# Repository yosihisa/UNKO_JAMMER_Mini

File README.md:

# UNKO_JAMMER_Mini  
UNKO_JAMMER_Mini is a camera infrared　remote control. It can also handle washlets.  
It is compatible with Nikon, Canon, Sony and LIXIL.  
This repository is the source code of infrared remote control of the camera. (With washlette jack function)  
Video is [here](https://twitter.com/n_yosihisa/status/977338885901508608).  

# ウンコジャマー ミニとは
ウンコジャマーはカメラ用赤外線リモコンです。ウォシュレットを操作することもできます。  
Niko・Canon,Sonyの撮影コマンドとLIXILのおしりコマンドに対応しています。  
PENTAXは今後のアップデートで対応予定です。  
動画は[こちら](https://twitter.com/n_yosihisa/status/977338885901508608)です。

## 各部名称  

## 使い方
### 準備 
コイン型リチウム電池(CR2032)を電池ボックスにセットします。  
電池の上にある黒いスイッチの白のつまみを利用するカメラのメーカーに合わせます。  

メーカー対応表  

|メーカー  |スイッチ1(上)  |スイッチ2(下)  |
|---|---|---|
|Nikon  |OFF(左)  |OFF(左)  |
|Canon  |ON (右)  |OFF(左)  |
|Sony   |OFF (左) |ON (右)  |
|PENTAX |ON (右)  |ON (右)  |

### 撮影する
カメラをリモコン操作モードにします。(各機種の取扱説明書をご覧ください。)  
左側のスライドスイッチをONにします。  
LEDの下にある白いボタンを押すとシャッターを切ることができます。  
撮影が終了したら左側のスライドスイッチをoFFにしましょう。  

### おしりコマンドを発動する
おしりコマンドを発動するためには白いボタンを押しながら電源を入れる必要があります。  
白いボタンを押したまま電源を入れると、電源を切るまで白いボタンを押すたびにおしりコマンドが送信されます。

## 開発環境
- Atmel Studio 7
- KiCad 5.0.0
## 作者
よしひさ([@n_yosihisa](https://twitter.com/n_yosihisa))  
てぽ丼([@teppodone](https://twitter.com/teppodone))

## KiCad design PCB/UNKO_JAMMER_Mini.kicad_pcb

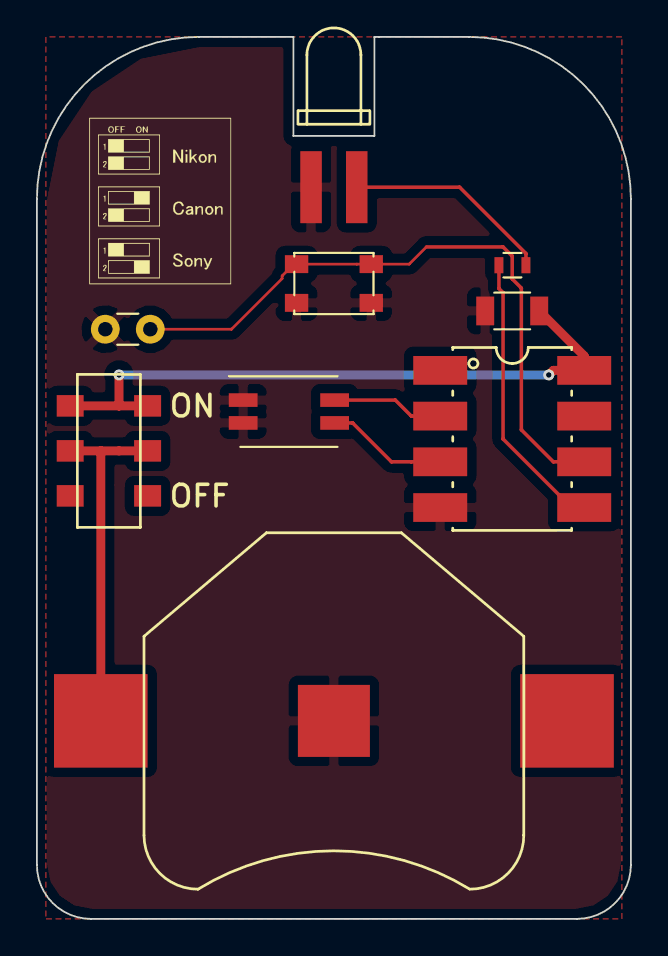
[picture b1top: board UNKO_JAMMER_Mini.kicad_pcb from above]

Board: 2 copper layers, 33.0 x 49.0 mm, 9 parts (0 on the bottom side), 8 nets.

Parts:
BT1: C2032; BC-2001
C1: 100u; C_1206
D1: LED; 3mmLED
IC1: ATTINY10-P; DIP_SMD-8
J1: Remote; C_Disc_D3.0mm_W1.6mm_P2.50mm
R1: 100; R_0603
SW1: POWER; SSSS213202_parallel
SW2: RELEASE; SKRPACE010_kai
SW3: ModeSelector; SW_DIP_x2_W5.08mm_Slide_Copal_CHS-A

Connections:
/LED: IC1.5, R1.1
/ModeSelect0: IC1.3, SW3.3
/ModeSelect1: IC1.2, SW3.4
/Release: IC1.6, J1.2, SW2.2
GND: BT1.2, C1.2, D1.1, IC1.4, J1.1, SW2.1, SW3.1, SW3.2
unnamed: BT1.1, SW1.2
unnamed: C1.1, IC1.8, SW1.3
unnamed: D1.2, R1.2

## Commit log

2018-12-11 NT kyoto 2018 version
2018-12-14 PENTAXに対応 スリープモード追加
